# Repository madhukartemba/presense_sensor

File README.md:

# Presence 1

Presence 1 is a mmWave radar–based presence sensor featuring an ambient light sensor, NeoPixel RGB LED, and capacitive touch switch.  
It is designed for seamless integration with Home Assistant.

Build commands:
Python version 3.12
Esphome version 2026.7.4
Example: esphome -s device_id 3 run prd/presence_1_basic/presence_1_basic.yaml

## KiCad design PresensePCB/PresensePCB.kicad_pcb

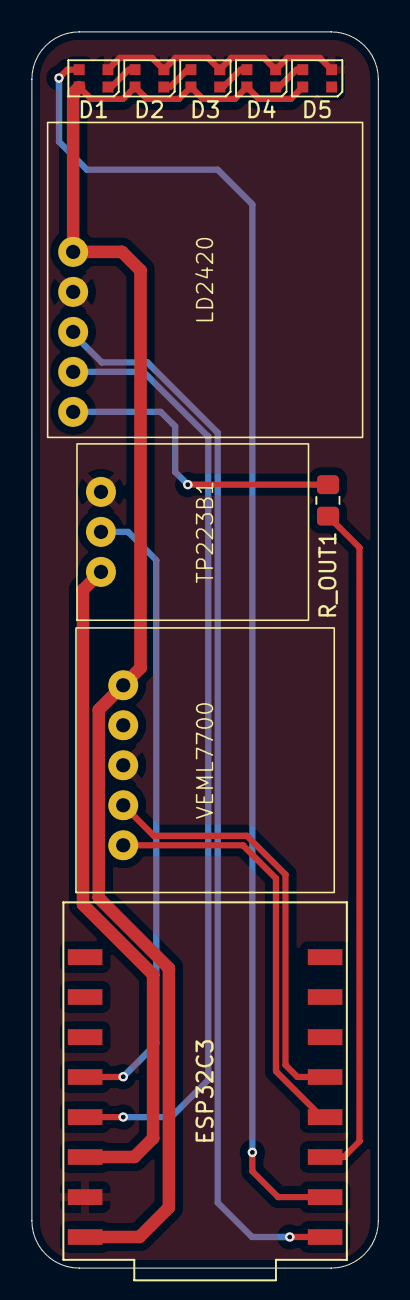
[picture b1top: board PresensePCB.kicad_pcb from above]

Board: 2 copper layers, 22.0 x 78.5 mm, 10 parts (0 on the bottom side), 15 nets.

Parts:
D1, D2, D3, D4, D5: WS2812B-2020; LED_WS2812B-2020_PLCC4_2.0x2.0mm
ESP32C3: ESP32-C3_SUPERMINI_TH; MODULE_ESP32-C3_SUPERMINI_TH
LD2420: LD2420_Module
R_OUT1: 0R; R_0805_2012Metric_Pad1.20x1.40mm_HandSolder
TP223B1: TP223B; TP223B_Module
VEML7700: VEML7700; VEML7700_Module

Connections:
+3.3V: ESP32C3.3.3 (3V3), TP223B1.1 (VCC)
+5V: D1.4 (VDD), D2.4 (VDD), D3.4 (VDD), D4.4 (VDD), D5.4 (VDD), ESP32C3.5V, LD2420.1 (VCC), VEML7700.1 (VCC)
G3: ESP32C3.3 (GPIO3), TP223B1.2 (OUT)
G4: ESP32C3.4 (GPIO4), LD2420.4 (RX)
G5: ESP32C3.5 (GPIO5), LD2420.3 (TX)
G6: D1.3 (DIN), ESP32C3.6 (GPIO6)
G7: ESP32C3.7 (GPIO7), R_OUT1.2
G8: ESP32C3.8 (GPIO8), VEML7700.5 (SDA)
G9: ESP32C3.9 (GPIO9), VEML7700.4 (SCL)
GND: D1.2 (VSS), D2.2 (VSS), D3.2 (VSS), D4.2 (VSS), D5.2 (VSS), ESP32C3.G (GND), LD2420.2 (GND), TP223B1.3 (GND), VEML7700.3 (GND)
unnamed: D1.1 (DOUT), D2.3 (DIN)
unnamed: D2.1 (DOUT), D3.3 (DIN)
unnamed: D3.1 (DOUT), D4.3 (DIN)
unnamed: D4.1 (DOUT), D5.3 (DIN)
unnamed: LD2420.5 (OUT), R_OUT1.1

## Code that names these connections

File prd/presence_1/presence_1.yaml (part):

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# I2C
# --------------------
i2c:
  sda: GPIO8
  scl: GPIO9
  scan: true
  frequency: 100kHz

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# --------------------
uart:
  id: uart_mmwave
  tx_pin: GPIO4
  rx_pin: GPIO5
  baud_rate: 115200
  parity: NONE
  stop_bits: 1
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  # PUSH BUTTON
  - platform: gpio
    pin:
      number: GPIO3
      mode: INPUT_PULLUP
      inverted: true
    internal: true
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
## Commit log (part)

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2026-02-01 Remove .DS_Store files
2026-02-01 add gitignore
2026-02-02 Revise README with new title and project details
    Updated project title and added a brief description.
2026-02-03 backup
2026-06-23 pairing mode strict mode fix
2026-06-23 upgrade to esphome2026.6.2
